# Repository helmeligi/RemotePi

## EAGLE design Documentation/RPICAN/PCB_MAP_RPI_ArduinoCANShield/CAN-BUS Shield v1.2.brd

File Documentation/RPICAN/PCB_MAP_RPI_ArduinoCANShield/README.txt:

This design is made by Mohamed MAGDY.
It is a PCB to enable the RPI to be connected physically to the CAN shield.

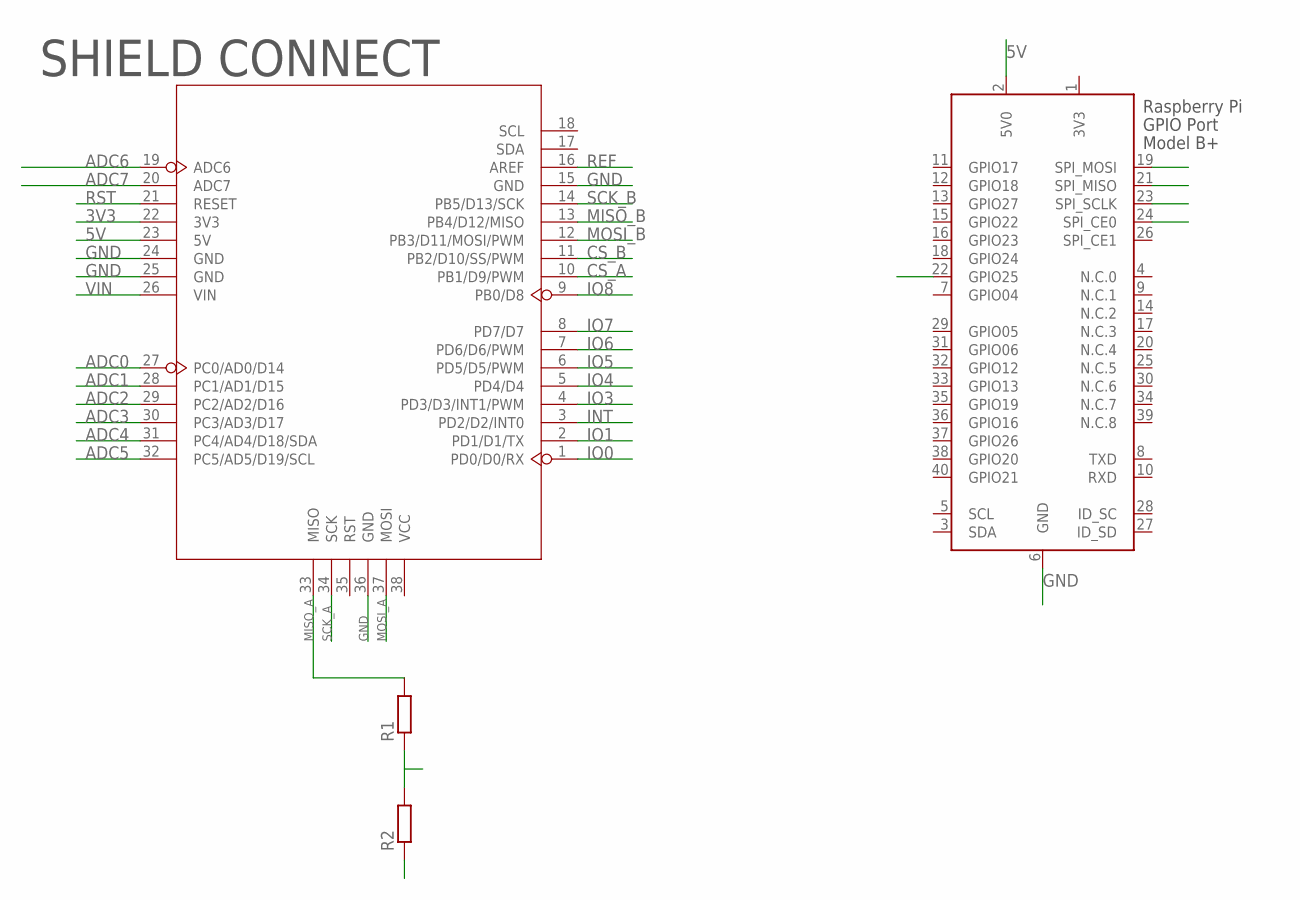
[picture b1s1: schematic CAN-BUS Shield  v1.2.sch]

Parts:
R1, R2: R0207/10; 0207/10
U3: ARDUINO-38P'WITH/-SILK'; ARDUINO-38P-WITH/-SILK-500519002
X2: RASPI_BOARD_B+_E0; RASPI_BOARD_B+_EDGES_0DRILL

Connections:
3V3: U3.22 (3V3), X2.1 (3V3)
5V: U3.23 (5V), X2.2 (5V0)
ADC0: U3.27 (PC0/AD0/D14)
ADC1: U3.28 (PC1/AD1/D15)
ADC2: U3.29 (PC2/AD2/D16)
ADC3: U3.30 (PC3/AD3/D17)
ADC4: U3.31 (PC4/AD4/D18/SDA)
ADC5: U3.32 (PC5/AD5/D19/SCL)
ADC6: U3.19 (ADC6)
ADC7: U3.20 (ADC7)
CS_A: U3.10 (PB1/D9/PWM)
CS_B: U3.11 (PB2/D10/SS/PWM), X2.24 (SPI_CE0)
GND: R2.1, U3.15 (GND), U3.24 (GND), U3.25 (GND), U3.36 (GND), X2.6 (GND)
INT: U3.3 (PD2/D2/INT0), X2.22 (GPIO25)
IO0: U3.1 (PD0/D0/RX)
IO1: U3.2 (PD1/D1/TX)
IO3: U3.4 (PD3/D3/INT1/PWM)
IO4: U3.5 (PD4/D4)
IO5: U3.6 (PD5/D5/PWM)
IO6: U3.7 (PD6/D6/PWM)
IO7: U3.8 (PD7/D7)
IO8: U3.9 (PB0/D8)
MISO_A: R1.2, U3.33 (MISO)
MISO_B: U3.13 (PB4/D12/MISO)
MISO_SCLD: R1.1, R2.2, X2.21 (SPI_MISO)
MOSI_A: U3.37 (MOSI), X2.19 (SPI_MOSI)
MOSI_B: U3.12 (PB3/D11/MOSI/PWM)
REF: U3.16 (AREF)
RST: U3.21 (RESET)
SCK_A: U3.34 (SCK), X2.23 (SPI_SCLK)
SCK_B: U3.14 (PB5/D13/SCK)
VIN: U3.26 (VIN)

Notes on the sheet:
SHIELD CONNECT

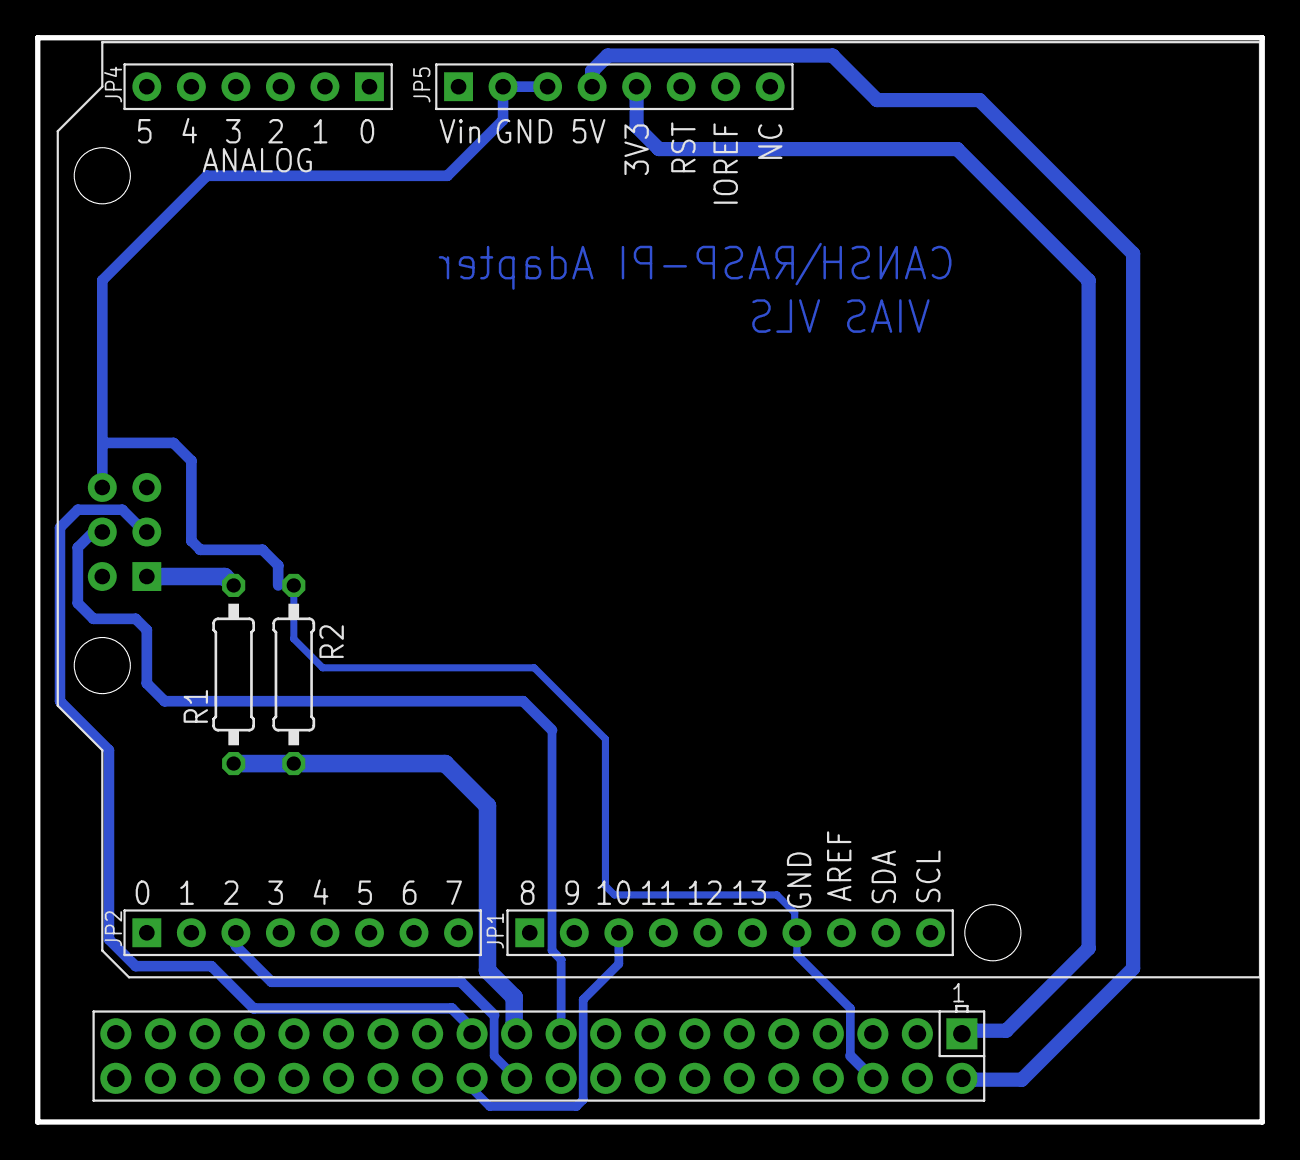
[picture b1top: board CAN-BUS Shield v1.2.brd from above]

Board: 2 copper layers, 69.8 x 61.8 mm, 4 parts (0 on the bottom side), 9 nets.

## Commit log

2020-07-03 Add the documentation for how to configure the RPI to work with Arduino CAN sheild to be able to send and recieve CAN frame on RPI
2020-07-03 Add the PCB design that was done by Mohamed MAGDY to enable the RPI to be connected physically to the Arduino CAN sheild
